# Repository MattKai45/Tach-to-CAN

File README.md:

# Tach-to-CAN
Engine RPM to CAN bus

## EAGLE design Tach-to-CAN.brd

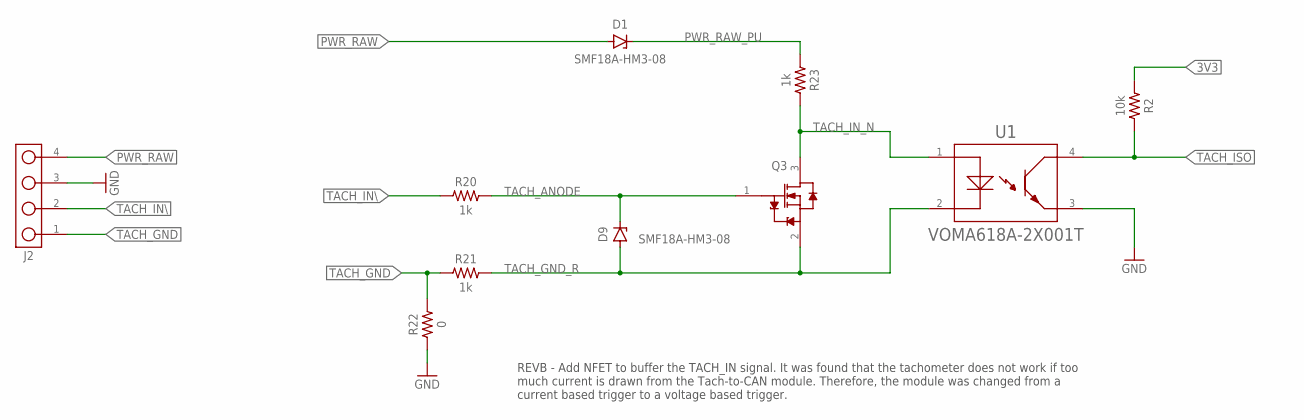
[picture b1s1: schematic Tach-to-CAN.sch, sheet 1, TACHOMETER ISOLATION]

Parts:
D1, D9: VISHAY_SMF18A-HM3-08; VISHAY_SMFXXA-HM3-08
J2: CONN_4PIN_VERT; CONN_100MIL_4_PIN
Q3: NEXPERIA_PMV60ENEAR; NXP_SOT23
R2: 10k; REST-0603
R20, R21, R23: 1k; REST-0603
R22: 0; REST-0603
U1: VISHAY_VOMA618A-2X001T; VISHAY_SOP-4

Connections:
3V3: R2.1; also elsewhere on the board
GND: J2.3, R22.1, U1.3; also elsewhere on the board
PWR_RAW: D1.A, J2.4; also elsewhere on the board
PWR_RAW_PU: D1.C, R23.1
TACH_ANODE: D9.C, Q3.1 (G), R20.2
TACH_GND: J2.1, R21.1, R22.2
TACH_GND_R: D9.A, Q3.2 (S), R21.2, U1.2
TACH_IN\: J2.2, R20.1
TACH_IN_N: Q3.3 (D), R23.2, U1.1
TACH_ISO: R2.2, U1.4; also elsewhere on the board

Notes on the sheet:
REVB - Add NFET to buffer the TACH_IN signal. It was found that the tachometer does not work if too much current is drawn from the Tach-to-CAN module. Therefore, the module was changed from a current based trigger to a voltage based trigger.

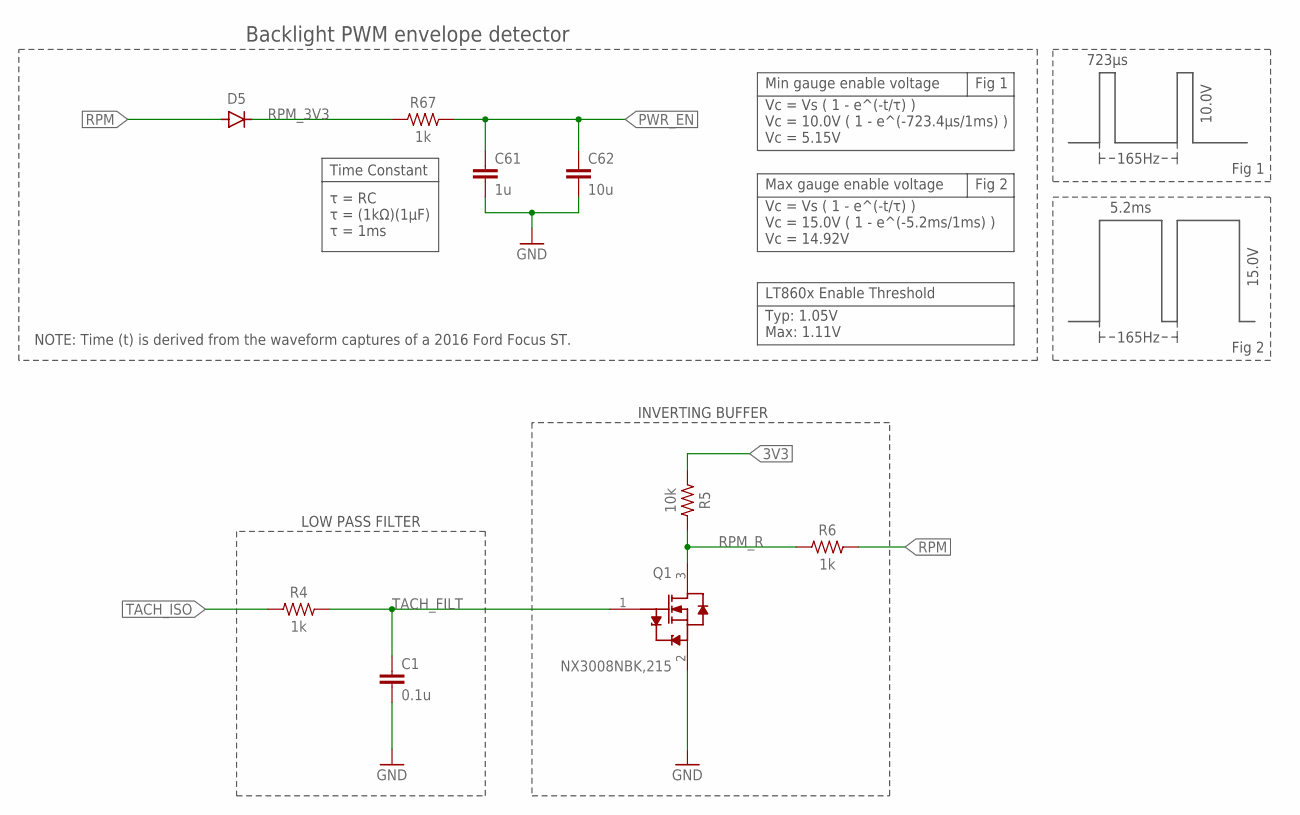
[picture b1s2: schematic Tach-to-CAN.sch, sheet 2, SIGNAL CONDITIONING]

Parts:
C1: 0.1u; CAP-0603
C61: 1u; CAP-0805
C62: 10u; CAP-1206
D5: AVX_SD1206S040S2R0
Q1: NXP_NX3008NBK,215NXP_SOT23; NXP_SOT23
R4, R6, R67: 1k; REST-0603
R5: 10k; REST-0603

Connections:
3V3: R5.1; also elsewhere on the board
GND: C1.2, C61.2, C62.2, Q1.2 (S); also elsewhere on the board
PWR_EN: C61.1, C62.1, R67.2; also elsewhere on the board
RPM: D5.A, R6.2; also elsewhere on the board
RPM_3V3: D5.C, R67.1
RPM_R: Q1.3 (D), R5.2, R6.1
TACH_FILT: C1.1, Q1.1 (G), R4.2
TACH_ISO: R4.1; also elsewhere on the board

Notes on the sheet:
LOW PASS FILTER
INVERTING BUFFER
Backlight PWM envelope detector
τ = RC τ = (1kΩ)(1µF) τ = 1ms
Vc = Vs ( 1 - e^(-t/τ) ) Vc = 10.0V ( 1 - e^(-723.4µs/1ms) ) Vc = 5.15V
Vc = Vs ( 1 - e^(-t/τ) ) Vc = 15.0V ( 1 - e^(-5.2ms/1ms) ) Vc = 14.92V
Max gauge enable voltage
Min gauge enable voltage
Time Constant
Typ: 1.05V Max: 1.11V
LT860x Enable Threshold
NOTE: Time (t) is derived from the waveform captures of a 2016 Ford Focus ST.
723µs
5.2ms
15.0V
10.0V
165Hz
Fig 1
Fig 2

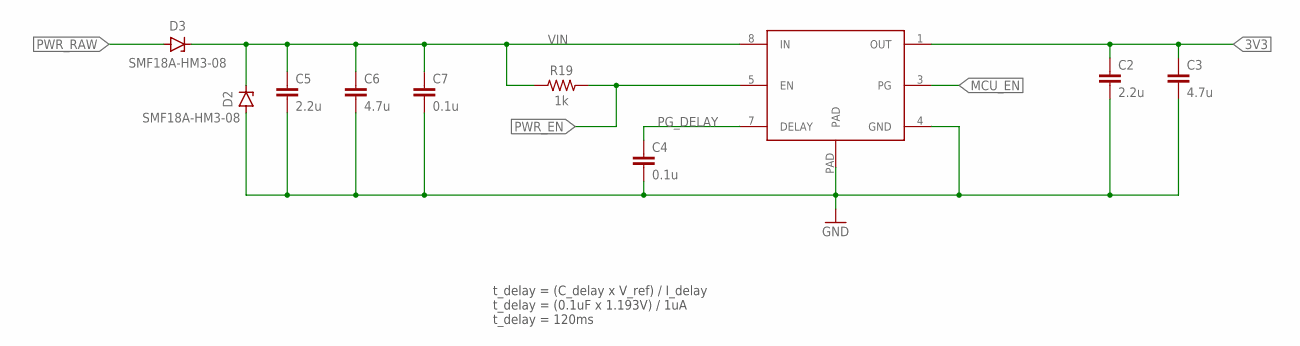
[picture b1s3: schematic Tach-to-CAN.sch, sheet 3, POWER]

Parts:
C2, C5: 2.2u; CAP-0805
C3, C6: 4.7u; CAP-1206
C4, C7: 0.1u; CAP-0603
D2, D3: VISHAY_SMF18A-HM3-08; VISHAY_SMFXXA-HM3-08
R19: 1k; REST-0603
U3: TI_TPS7A1633AQDGNRQ1; TI_MSSOP8

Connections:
3V3: C2.1, C3.1, U3.1 (OUT); also elsewhere on the board
GND: C2.2, C3.2, C4.2, C5.2, C6.2, C7.2, D2.A, U3.4 (GND), U3.PAD; also elsewhere on the board
MCU_EN: U3.3 (PG); also elsewhere on the board
PG_DELAY: C4.1, U3.7 (DELAY)
PWR_EN: R19.2, U3.5 (EN); also elsewhere on the board
PWR_RAW: D3.A; also elsewhere on the board
VIN: C5.1, C6.1, C7.1, D2.C, D3.C, R19.1, U3.8 (IN)

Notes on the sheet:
t_delay = (C_delay x V_ref) / I_delay t_delay = (0.1uF x 1.193V) / 1uA t_delay = 120ms

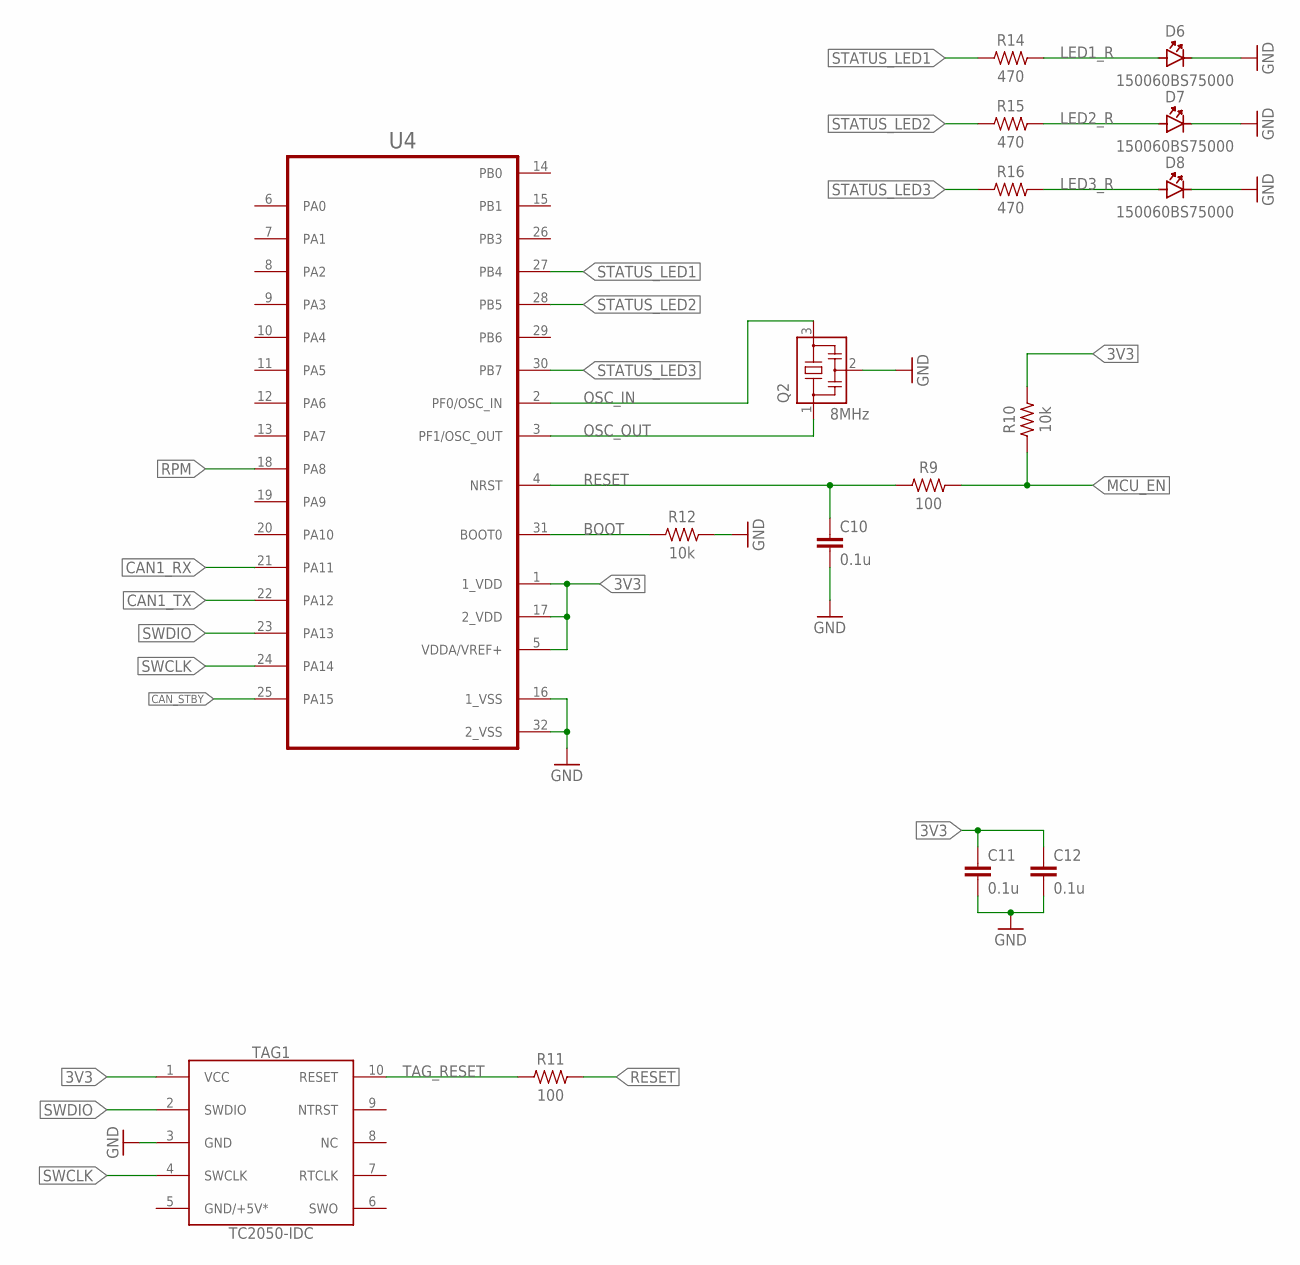
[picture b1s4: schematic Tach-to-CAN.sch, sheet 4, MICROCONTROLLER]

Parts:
C10, C11, C12: 0.1u; CAP-0603
D6, D7, D8: LED_BLUE_0603_WURTH; WURTH_0603_LED
Q2: 8MHz; CSTCR6M
R9, R11: 100; REST-0603
R10, R12: 10k; REST-0603
R14, R15, R16: 470; REST-0603
TAG1: TC2050-IDC
U4: STM32F303K8T6STMICROELECTRONICS_STM32F303K8T6; STM32F303K8T6

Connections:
3V3: C11.1, C12.1, R10.2, TAG1.1 (VCC), U4.1 (1_VDD), U4.5 (VDDA/VREF+), U4.17 (2_VDD); also elsewhere on the board
BOOT: R12.1, U4.31 (BOOT0)
CAN1_RX: U4.21 (PA11); also elsewhere on the board
CAN1_TX: U4.22 (PA12); also elsewhere on the board
CAN_STBY: U4.25 (PA15); also elsewhere on the board
GND: C10.2, C11.2, C12.2, D6.C, D7.C, D8.C, Q2.2, R12.2, TAG1.3 (GND), U4.16 (1_VSS), U4.32 (2_VSS); also elsewhere on the board
LED1_R: D6.A, R14.2
LED2_R: D7.A, R15.2
LED3_R: D8.A, R16.2
MCU_EN: R9.2, R10.1; also elsewhere on the board
OSC_IN: Q2.3, U4.2 (PF0/OSC_IN)
OSC_OUT: Q2.1, U4.3 (PF1/OSC_OUT)
RESET: C10.1, R9.1, R11.2, U4.4 (NRST)
RPM: U4.18 (PA8); also elsewhere on the board
STATUS_LED1: R14.1, U4.27 (PB4)
STATUS_LED2: R15.1, U4.28 (PB5)
STATUS_LED3: R16.1, U4.30 (PB7)
SWCLK: TAG1.4 (SWCLK), U4.24 (PA14)
SWDIO: TAG1.2 (SWDIO), U4.23 (PA13)
TAG_RESET: R11.1, TAG1.10 (RESET)

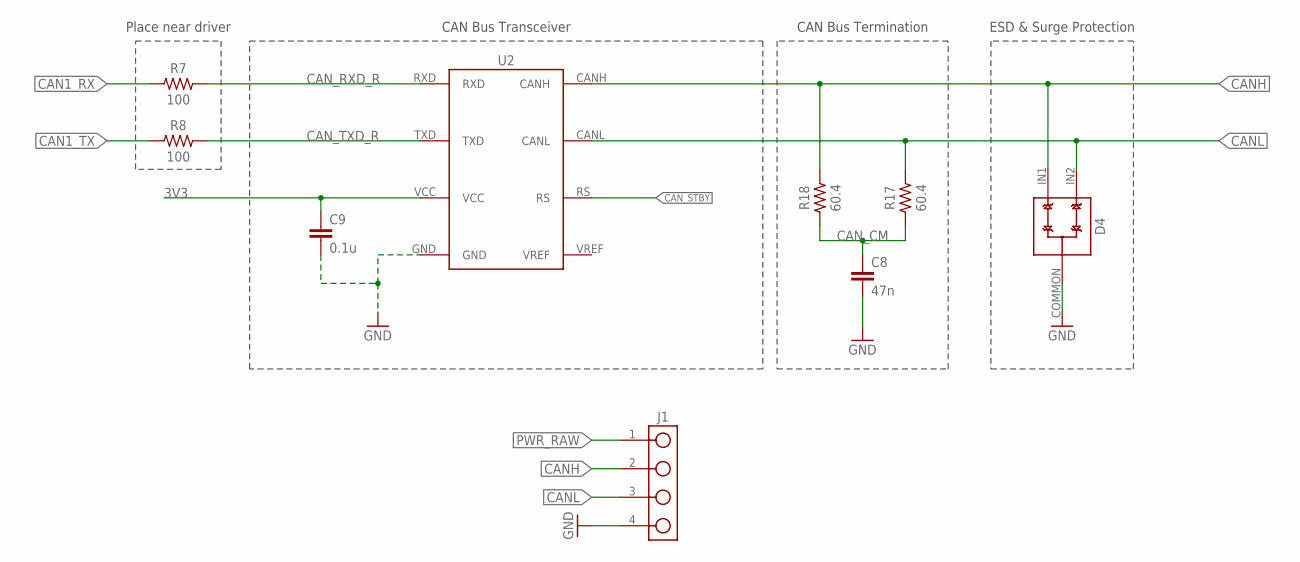
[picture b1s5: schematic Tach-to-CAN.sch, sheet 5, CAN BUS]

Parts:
C8: 47n; CAP-0603
C9: 0.1u; CAP-0603
D4: CDSOT23-T24CAN-Q; BOURNS_CDSOT23-T24CAN-Q
J1: CONN_4PIN_VERT; CONN_100MIL_4_PIN
R7, R8: 100; REST-0603
R17, R18: 60.4; REST-0603
U2: TI_SN65HVD23X

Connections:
3V3: C9.1, U2.VCC; also elsewhere on the board
CAN1_RX: R7.1; also elsewhere on the board
CAN1_TX: R8.1; also elsewhere on the board
CANH: D4.IN1 (IN2), J1.2, R18.2, U2.CANH
CANL: D4.IN2 (IN1), J1.3, R17.2, U2.CANL
CAN_CM: C8.1, R17.1, R18.1
CAN_RXD_R: R7.2, U2.RXD
CAN_STBY: U2.RS; also elsewhere on the board
CAN_TXD_R: R8.2, U2.TXD
GND: C8.2, C9.2, D4.COMMON (OUT), J1.4, U2.GND; also elsewhere on the board
PWR_RAW: J1.1; also elsewhere on the board

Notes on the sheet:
ESD & Surge Protection
CAN Bus Termination
CAN Bus Transceiver
Place near driver

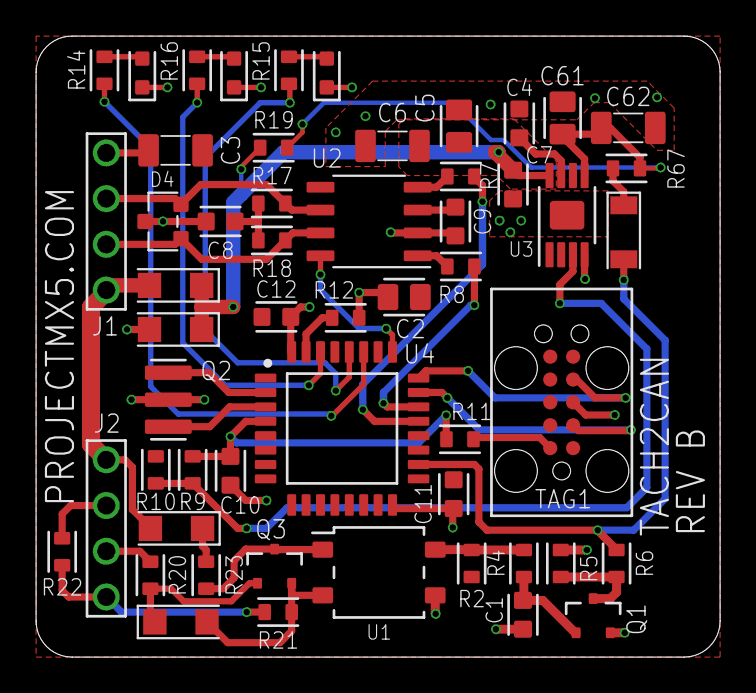
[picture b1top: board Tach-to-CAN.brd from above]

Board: 2 copper layers, 38.0 x 34.5 mm, 54 parts (0 on the bottom side), 39 nets.

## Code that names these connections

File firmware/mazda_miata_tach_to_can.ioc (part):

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Mcu.Name=STM32F303K(6-8)Tx
Mcu.Package=LQFP32
Mcu.UserName=STM32F303K8Tx
PA11.Mode=Master
PA11.Signal=CAN_RX
PA12.Mode=Master
PA12.Signal=CAN_TX
PA13.GPIOParameters=GPIO_Label
PA13.GPIO_Label=SWDIO
PA13.Mode=Serial_Wire
PA13.Signal=SYS_JTMS-SWDIO
PA14.GPIOParameters=GPIO_Label
PA14.GPIO_Label=SWCLK
PA14.Mode=Serial_Wire
PA14.Signal=SYS_JTCK-SWCLK
PA15.GPIOParameters=PinState,GPIO_Label
PA15.GPIO_Label=CAN_STBY
PA15.PinState=GPIO_PIN_RESET
PA15.Signal=GPIO_Output
PA2.GPIOParameters=GPIO_Label
PA2.GPIO_Label=VCP_TX
PA2.Signal=USART2_TX
PA8.Signal=S_TIM1_CH1
PB4.GPIOParameters=GPIO_Speed,PinState,GPIO_PuPd,GPIO_Label,GPIO_ModeDefaultOutputPP
PB4.GPIO_Label=LED1
PB4.GPIO_ModeDefaultOutputPP=GPIO_MODE_OUTPUT_PP
PB4.GPIO_PuPd=GPIO_NOPULL
PB4.GPIO_Speed=GPIO_SPEED_FREQ_LOW
PB4.PinState=GPIO_PIN_RESET
PB4.Signal=GPIO_Output
PB5.GPIOParameters=GPIO_Speed,PinState,GPIO_PuPd,GPIO_Label,GPIO_ModeDefaultOutputPP
PB5.GPIO_Label=LED2
PB5.GPIO_ModeDefaultOutputPP=GPIO_MODE_OUTPUT_PP
PB5.GPIO_PuPd=GPIO_NOPULL
PB5.GPIO_Speed=GPIO_SPEED_FREQ_LOW
PB5.PinState=GPIO_PIN_RESET
PB5.Signal=GPIO_Output
PB7.GPIOParameters=GPIO_Speed,PinState,GPIO_PuPd,GPIO_Label,GPIO_ModeDefaultOutputPP
PB7.GPIO_Label=LED3
PB7.GPIO_ModeDefaultOutputPP=GPIO_MODE_OUTPUT_PP
PB7.GPIO_PuPd=GPIO_NOPULL
PB7.GPIO_Speed=GPIO_SPEED_FREQ_LOW
PB7.PinState=GPIO_PIN_RESET
PB7.Signal=GPIO_Output
RCC.HSEPLLFreq_Value=8000000
RCC.HSE_VALUE=8000000
RCC.SYSCLKFreq_VALUE=16000000
RCC.SYSCLKSourceVirtual=RCC_SYSCLKSOURCE_PLLCLK
board=NUCLEO-F303K8
boardIOC=true

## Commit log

2020-04-09 Board and Schematic initial commit
2021-11-16 Initial commit of firmware
2021-11-16 Update Eagle project info
2021-11-16 Add NFET to buffer TACH_IN signal
2022-01-21 Update copyright year to 2022
2022-01-21 Update device to use internal clock
2022-01-21 Calibrate frequency measurements
2022-01-21 Return 1:1 Engine RPM values on the CAN bus
2022-01-22 Indicate an error occurred when the Error_Handler is called
2022-01-22 Code cleanup
